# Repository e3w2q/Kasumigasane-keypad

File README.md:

# Kasumigasane (霞襲)

## What is Kasumigasane?

Kasumigasane is a simple 16-key keypad that can be assembled without diodes.

*Kasumigasane* (霞襲) means "a layer of misty stuff", because it is made of layers of glass exposi substrates.

## Customizability

You can choose a frame from eight different patterns.

You can decorate the sides with 15mm wide masking tape.

The rightmost column and the lowermost row can use the 2U key.

The upper leftmost key can be replaced by a rotary encoder.

Backlight LED can be soldered.

## Link

[Hardware data (PCB)](pcb/)

[Firmware](https://github.com/e3w2q/qmk_firmware/tree/e3w2q/keyboards/e3w2q/kasumigasane)

[PCBの入手方法](doc/pcb_order_guide_jp.md)

[パーツリスト](doc/bom_list_jp.md)

[ビルドガイド](doc/readme_jp.md)

## Short Story

キーの上に指を走らせる。画面に文字が浮かび上がり、文章が出力されていく。つくづく現代、キータイプという作業と仕事は切り離せない関係になった。私のような文筆業のものにとっては、尚更である。<br />
キーボードは、ハードウェアと人間を繋ぐインターフェースのなかでもかなり原始的な部類のものだ。起源としては一八七三年に登場したタイプライターだが、日本語のワード・プロセッサーが登場したのは比較的最近の一九七九年。それでもおおよそ五〇年間、人間はこのデバイスと付き合ってきたと言っていい。<br />
その中でキーボードは進化を遂げてきた。キーボードは極論、『打った内容を正確にハードウェアに伝える』——ただそのためだけの役割の道具だが、人間の手に最も長い時間触れるデバイスの一つである。<br />
数々の高級キーボードが、進化の中で姿を現した。人間工学に配慮したもの、あるいは打鍵感を追求したもの、外見の高級感を備えたもの——近年では、自分に合うものをこそ自作しよう、という風潮まである。キーボードは簡単な電子回路と物理的接点、即ちスイッチがあれば実装できるデバイスでもある為だ。<br />
キリのいいところまで原稿を進めて、左手を横にスライドさせる。<br />
私は、目を走らせることなく、メインキーボードの横にあるキーを叩いた。——見ずとも打てるほどに慣れた配置。<br />
そう。メインキーボードの横には、四×四のオーソリニア・レイアウトをしたテンキーが鎮座している。これもまた、件の自作キーボードの一つだ。ベースは黒の落ち着いた筐体。好みでキートップはチェッカーフラッグ様の配色としてある。<br />
キー押下一つで、マクロが走り、エディタの校閲機能が起動、文章を精査する。——これも自作キーボードの魅力の一つだ。ユーザーがマクロ機能を作り込むことで、この小さなテンキーは作業効率を大きく変えうるワイルドカードとなる。<br />
あぶり出された誤字と誤用を、テンキー操作でジャンプしながら修正していく。<br />
明日も、明後日も、この小さな相棒は、私の手の左で、辣腕の執事のように活躍の機会を待っていてくれるだろう。<br />
——このテンキーの名前は、霞襲（かすみがさね）。

## Photos

<small>Photo by @otahinosame</small>

<small>Photo by @k2\_\_\_\_\_\_\_\_\_\_\_</small>

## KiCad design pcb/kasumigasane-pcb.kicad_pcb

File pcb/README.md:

# Kasumigasane PCB Data

## Schematic

## PCB Layout

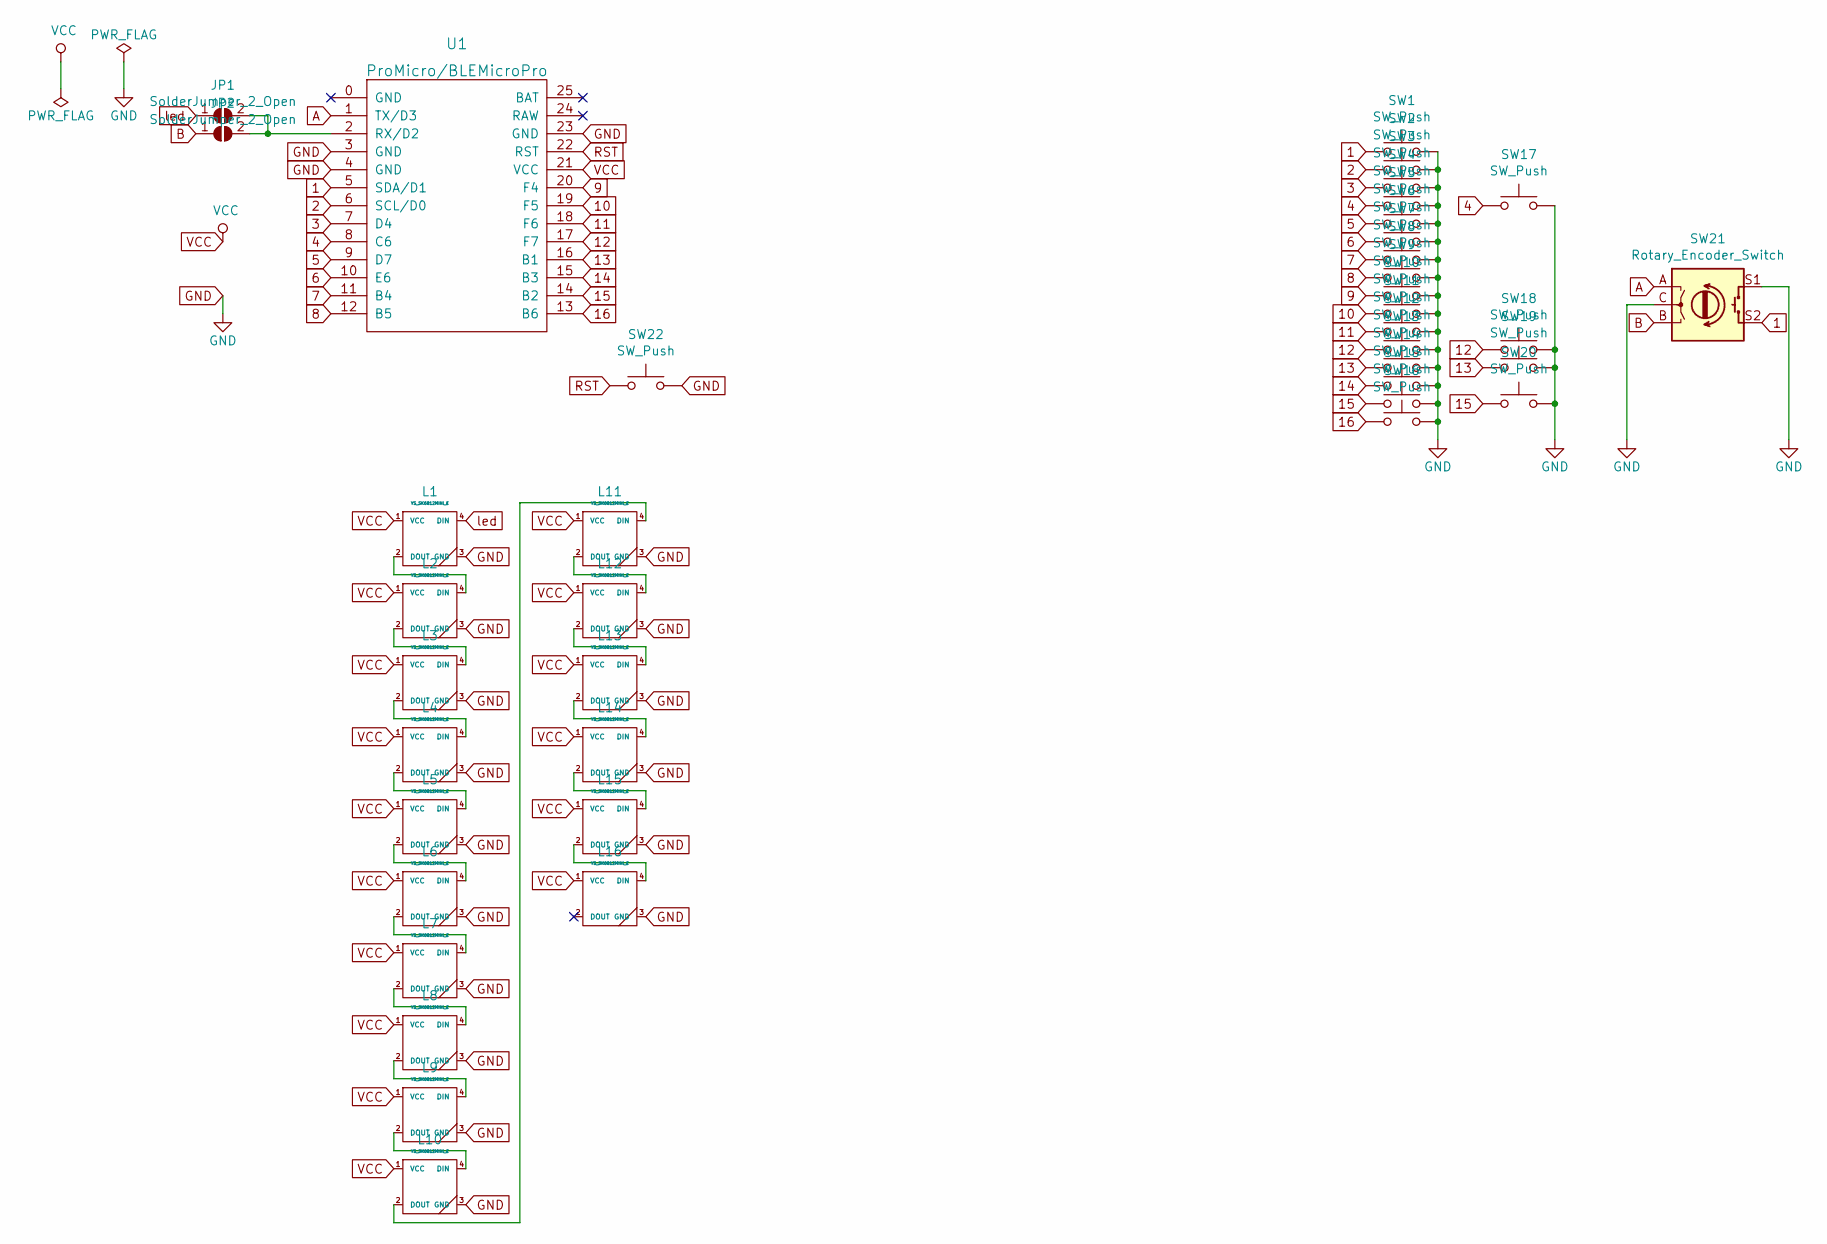
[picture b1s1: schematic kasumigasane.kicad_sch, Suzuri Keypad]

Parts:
JP1, JP2: SolderJumper_2_Open; SolderJumper-2_P1.3mm_Open_Pad1.0x1.0mm
L1, L2, L3, L4, L5, L6, L7, L8, L9, L10, L11, L12, L13, L14, L15, L16: YS_SK6812MINI_E; YS-SK6812MINI-E
SW1, SW2, SW3, SW4, SW5, SW6, SW7, SW8, SW9, SW10, SW11, SW12, SW13, SW14, SW15, SW16, SW17, SW18, SW19, SW20: SW_Push; CherryMX
SW21: Rotary_Encoder_Switch; RotaryEncoder_Alps_EC11E-Switch_Vertical_H20mm_rev2
SW22: SW_Push; ResetSW
U1: ProMicro/BLEMicroPro; ArduinoProMicro_ConThrough

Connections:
1: SW1.1, SW21.S2, U1.5 (SDA/D1)
2: SW2.1, U1.6 (SCL/D0)
3: SW3.1, U1.7 (D4)
4: SW4.1, SW17.1, U1.8 (C6)
5: SW5.1, U1.9 (D7)
6: SW6.1, U1.10 (E6)
7: SW7.1, U1.11 (B4)
8: SW8.1, U1.12 (B5)
9: SW9.1, U1.20 (F4)
10: SW10.1, U1.19 (F5)
11: SW11.1, U1.18 (F6)
12: SW12.1, SW18.1, U1.17 (F7)
13: SW13.1, SW19.1, U1.16 (B1)
14: SW14.1, U1.15 (B3)
15: SW15.1, SW20.1, U1.14 (B2)
16: SW16.1, U1.13 (B6)
A: SW21.A, U1.1 (TX/D3)
B: JP2.1 (A), SW21.B
GND: L1.3 (GND), L2.3 (GND), L3.3 (GND), L4.3 (GND), L5.3 (GND), L6.3 (GND), L7.3 (GND), L8.3 (GND), L9.3 (GND), L10.3 (GND), L11.3 (GND), L12.3 (GND), L13.3 (GND), L14.3 (GND), L15.3 (GND), L16.3 (GND), SW1.2, SW2.2, SW3.2, SW4.2, SW5.2, SW6.2, SW7.2, SW8.2, SW9.2, SW10.2, SW11.2, SW12.2, SW13.2, SW14.2, SW15.2, SW16.2, SW17.2, SW18.2, SW19.2, SW20.2, SW21.C, SW21.S1, SW22.2, U1.3 (GND), U1.4 (GND), U1.23 (GND)
unnamed: JP1.2 (B), JP2.2 (B), U1.2 (RX/D2)
unnamed: L1.2 (DOUT), L2.4 (DIN)
unnamed: L2.2 (DOUT), L3.4 (DIN)
unnamed: L3.2 (DOUT), L4.4 (DIN)
unnamed: L4.2 (DOUT), L5.4 (DIN)
unnamed: L5.2 (DOUT), L6.4 (DIN)
unnamed: L6.2 (DOUT), L7.4 (DIN)
unnamed: L7.2 (DOUT), L8.4 (DIN)
unnamed: L8.2 (DOUT), L9.4 (DIN)
unnamed: L10.2 (DOUT), L11.4 (DIN)
unnamed: L9.2 (DOUT), L10.4 (DIN)
unnamed: L11.2 (DOUT), L12.4 (DIN)
unnamed: L12.2 (DOUT), L13.4 (DIN)
unnamed: L13.2 (DOUT), L14.4 (DIN)
unnamed: L14.2 (DOUT), L15.4 (DIN)
unnamed: L15.2 (DOUT), L16.4 (DIN)
RST: SW22.1, U1.22 (RST)
VCC: L1.1 (VCC), L2.1 (VCC), L3.1 (VCC), L4.1 (VCC), L5.1 (VCC), L6.1 (VCC), L7.1 (VCC), L8.1 (VCC), L9.1 (VCC), L10.1 (VCC), L11.1 (VCC), L12.1 (VCC), L13.1 (VCC), L14.1 (VCC), L15.1 (VCC), L16.1 (VCC), U1.21 (VCC)
led: JP1.1 (A), L1.4 (DIN)

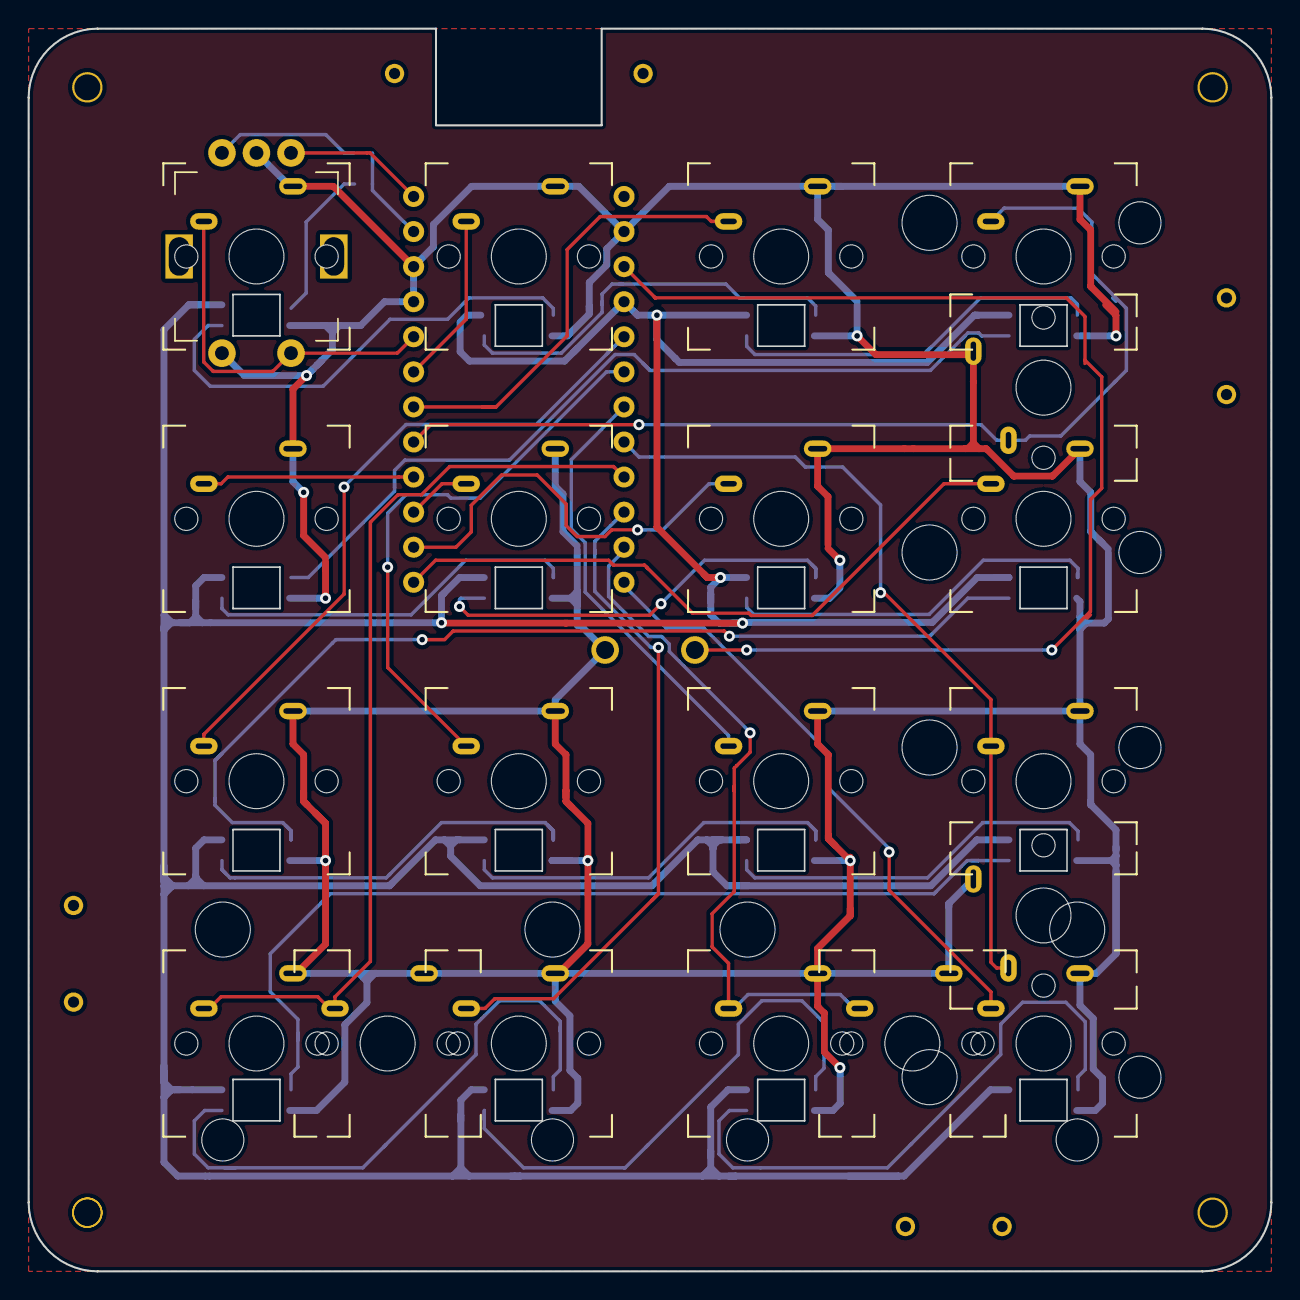
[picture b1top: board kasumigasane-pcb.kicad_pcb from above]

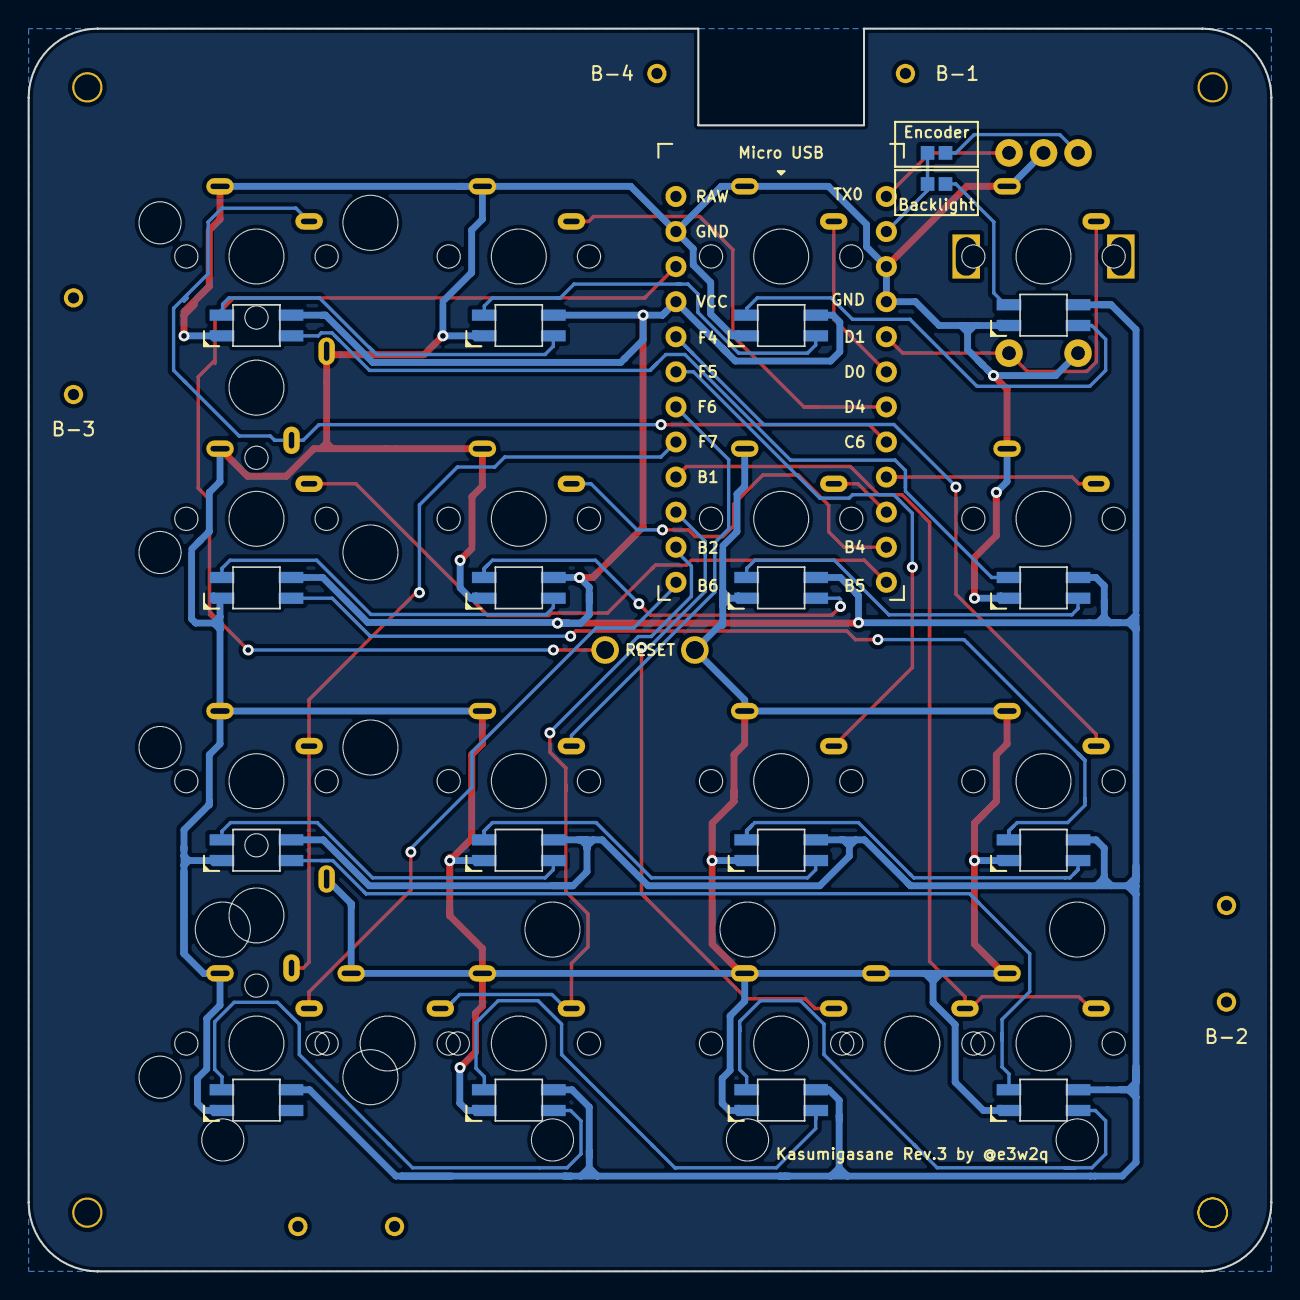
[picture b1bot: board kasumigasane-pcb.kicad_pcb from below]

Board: 2 copper layers, 90.0 x 90.0 mm, 41 parts (4 on the bottom side), 38 nets.

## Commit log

2021-08-29 Rev3
2021-08-31 Upload PCB data
2021-09-06 Update documents
2021-09-07 Update firmware
2021-09-12 Add photos
2021-10-15 Fix typo

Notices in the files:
README.md:
License: MIT
